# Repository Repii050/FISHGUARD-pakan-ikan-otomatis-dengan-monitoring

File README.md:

# FISHGUARD
<!DOCTYPE html>
<html lang="id">
<head>
    <meta charset="UTF-8">
    <meta name="viewport" content="width=device-width, initial-scale=1.0">
    <meta http-equiv="X-UA-Compatible" content="ie=edge">
    
</head>
<body>
    <div class="container">
        <h1>Rancang bangun pakan ikan otomatis dengan monitoring realtime </h1>
        <p>Ikan Hias dikenal sebagai salah satu spesies ikan yang banyak di budidayakan dan memiliki nilai ekonomis tinggi. Namun, ikan Hias juga memerlukan kondisi lingkungan yang sangat spesifik dan stabil agar dapat tumbuh dengan baik. Fluktuasi suhu air, perubahan kadar pH, serta rendahnya kadar oksigen dalam air dapat berdampak negatif pada kesehatan ikan.</p>
        <h1>Didukung Oleh :</h1>
<p> Dosen Pengampu : Akhmad Hendriawan ST., MT. (NIP.197501272002121003)</p>
<p>Mata kuliah : IoT dan Jaringan Sensor </p><br>
<p>Program Studi : D4 Teknik Elektronika</p><br>
<p>Politeknik Elektronika Negeri Surabaya</p><br>
        <h2>Daftar Nama Anggota Team</h2>  
    <table>
        <thead>
            <tr>
                <th>Nomor</th>
                <th>Nama</th>
                <th>NRP</th>
                <th>Jobdesk</th>
                <th>Nama Akun</th>
                <th>Link Akun</th>
            </tr>
        </thead>
        <tbody>
            <tr>
                <td align = center>1</td>
                <td>Alwansyah Muhammad M.E</td>
                <td>2122600031</td>
                <td>Project Sales</td>
                <td>alwansyahendrawan</td>
                <td>https://github.com/alwansyahendrawan</td>
            </tr>
            <tr>
                <td align = center>2</td>
                <td>I Gede Wahyu Satria Nugraha </td>
                <td>2122600033</td>
                <td>UI/UX Desain</td>
                <td>Gedewsnnn</td>
                <td>https://github.com/Gedewsnnn</td>
            </tr>
            <tr>
                <td align = center>3</td>
                <td>Rafi Satrio</td>
                <td>2122600050</td>
                <td>Hardware Developer</td>
                <td>Repii050</td>
                <td>https://github.com/Repii050</td>
            </tr>
                <tr>
                <td align = center>4</td>
                <td>Dewangga Pratama Ikko Prasetyo</td>
                <td>2122600052</td>
                <td>Data Analyst</td>
                <td>DewanggaPIP</td>
                <td>https://github.com/DewanggaPIP</td>
            </tr>
                <tr>
                <td align = center>5</td>
                <td>Wildan Aldi Nugroho</td>
                <td>2122600055</td>
                <td>Software Developer</td>
                <td>Wildan-Aldi</td>
                <td>https://github.com/Wildan-Aldi</td>
            </tr>
             <tr>
                <td align = center>6</td>
                <td> Dera Berlian </td>
                <td>2122600057</td>
                <td>Project Manager</td>
                <td>DeraBerlian</td>
                <td>https://github.com/DeraBerlian</td>
            </tr>
        </tbody>
    </table>
<h1>Hardware </h1>
<p>Berikut ini adalah hasil skematik rangkaian FishGuard menggunakan software Eagle.</p>
        
<br>
 <p>Berikut ini adalah hasil Board PCB rangkaian FishGuard menggunakan software Eagle.</p><br>                                                                                                                                                               
<br>
<h1>Desain 3D </h1>
1. Desain 3D Tampak Depan <br>

2. Desain 3D Tampak Samping <br>

3. Desain 3D Tampak Belakang <br>

# ANGGOTA KELOMPOK FISH GUARD

# Fleyer

# Link Video Iklan : 
https://youtube.com/shorts/qlZNBy3aBwo?feature=share

# Link Video Pengujian Sistem : 
https://youtu.be/G6Ex1cATNBE

# Link Video Presentasi : 
https://youtu.be/gjWip73ETbg
# Software Aplikasi
https://github.com/Repii050/FISHGUARD-pakan-ikan-otomatis-dengan-monitoring/tree/main/Aplikasi
# DATA 
https://github.com/Repii050/FISHGUARD-pakan-ikan-otomatis-dengan-monitoring/tree/main/Data
# Desain dan Perencanaan 
https://github.com/Repii050/FISHGUARD-pakan-ikan-otomatis-dengan-monitoring/tree/main/Desain%20dan%20Perencanaan
# Hardware
https://github.com/Repii050/FISHGUARD-pakan-ikan-otomatis-dengan-monitoring/tree/main/Hardware#readme
# diagram sistem

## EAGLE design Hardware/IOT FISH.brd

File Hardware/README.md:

# Video Pengujian Komponen

Berikut adalah beberapa video serta progam yang digunakan dalam pengujian berbagai komponen sistem FishGuard.

## FishGuard - Pengujian Servo
https://github.com/user-attachments/assets/23995870-86eb-4068-b8aa-cf2c34f3a0c6

### Program Pengujian servo
Program ini berfungsi untuk melakukan pengujian dengan mengendalikan sebuah servo motor menggunakan Arduino, menggerakkannya dari sudut 0° hingga 180° dan kembali, sambil menampilkan posisi aktuator pada Serial Monitor.
```cpp
#include <Servo.h>

// Membuat objek servo
Servo myServo;

// Mendefinisikan pin servo
const int servoPin = 9;

void setup() {
  // Menentukan pin servo dan menginisialisasi servo
  myServo.attach(servoPin);

  // Memulai komunikasi serial untuk menampilkan posisi di Serial Monitor
  Serial.begin(9600);
}

void loop() {
  // Menggerakkan servo dari 0° ke 180°
  for (int pos = 0; pos <= 180; pos += 1) { // Inkrementasi 1 derajat
    myServo.write(pos);
    Serial.print("Posisi Servo: ");
    Serial.print(pos);
    Serial.println(" derajat");
    delay(15); // Tunggu 15 ms agar servo memiliki waktu untuk bergerak
  }

  // Menggerakkan servo dari 180° ke 0°
  for (int pos = 180; pos >= 0; pos -= 1) { // Dekrementasi 1 derajat
    myServo.write(pos);
    Serial.print("Posisi Servo: ");
    Serial.print(pos);
    Serial.println(" derajat");
    delay(15); // Tunggu 15 ms agar servo memiliki waktu untuk bergerak
  }
}
```

## FishGuard - Pengujian Sensor Ultrasonic HC-SR04
https://github.com/user-attachments/assets/480f4f2f-f9c4-4a9e-84b7-378d93c347e1

### Program Pengujian Sensor Ultrasonic HC-SR04
Program ini berfungsi untuk melakukan pengujian dengan mengukur jarak.
```cpp
// Mendefinisikan pin Trig dan Echo
const int trigPin = 9;
const int echoPin = 10;

// Variabel untuk menyimpan hasil pengukuran jarak
long duration;
float distance;

void setup() {
  // Inisialisasi komunikasi serial
  Serial.begin(9600);

  // Mengatur pin trigPin sebagai output dan echoPin sebagai input
  pinMode(trigPin, OUTPUT);
  pinMode(echoPin, INPUT);
}

void loop() {
  // Membersihkan pin trigPin
  digitalWrite(trigPin, LOW);
  delayMicroseconds(2);

  // Mengirimkan sinyal trigger selama 10 mikrodetik
  digitalWrite(trigPin, HIGH);
  delayMicroseconds(10);
  digitalWrite(trigPin, LOW);

  // Membaca durasi waktu dari sinyal yang diterima oleh echoPin
  duration = pulseIn(echoPin, HIGH);

  // Menghitung jarak (dalam cm) berdasarkan waktu tempuh sinyal
  distance = duration * 0.034 / 2;

  // Menampilkan hasil pengukuran jarak di Serial Monitor
  Serial.print("Jarak: ");
  Serial.print(distance);
  Serial.println(" cm");

  delay(500); // Delay 0,5 detik untuk stabilitas pembacaan
}
```

## FishGuard - Pengujian Sensor DS18B20 Suhu
https://github.com/user-attachments/assets/f8e08aa3-e3c8-4e6e-869c-6c9238689587

### Program Sensor DS18B20 Suhu
Program ini berfungsi untuk melakukan pengujian dengan membaca suhu dari sensor DS18B20 menggunakan Arduino, dan menampilkan hasilnya di Serial Monitor. Sensor ini terhubung melalui protokol OneWire.
```cpp
#include <OneWire.h>
#include <DallasTemperature.h>

// Pin yang terhubung ke pin DATA DS18B20
const int dataPin = 2;

// Membuat instance dari OneWire
OneWire oneWire(dataPin);

// Membuat instance dari DallasTemperature
DallasTemperature sensors(&oneWire);

void setup() {
  // Memulai komunikasi serial
  Serial.begin(9600);

  // Memulai sensor DS18B20
  sensors.begin();
}

void loop() {
  // Meminta sensor untuk melakukan pembacaan suhu
  sensors.requestTemperatures();

  // Membaca suhu dalam Celsius dari sensor pertama (index 0)
  float temperatureC = sensors.getTempCByIndex(0);

  // Menampilkan suhu di Serial Monitor
  Serial.print("Suhu: ");
  Serial.print(temperatureC);
  Serial.println(" °C");

  delay(1000); // Membaca suhu setiap 1 detik
}
```

## FishGuard - Pengujian Sensor TDS Meter
https://github.com/user-attachments/assets/90e463b5-ef5b-4650-b92f-95f3acb5ff2d

### Program Pengujian Sensor TDS Meter
Program ini berfungsi untuk melakukan pengujian dengan membaca nilai Total Dissolved Solids (TDS) dalam larutan menggunakan sensor TDS yang terhubung ke pin analog Arduino. TDS mengukur jumlah partikel terlarut (seperti mineral dan garam) dalam air, biasanya dinyatakan dalam ppm (parts per million).
```cpp
// Mendefinisikan pin analog yang terhubung ke sensor TDS
const int tdsPin = A0; 

// Tegangan input referensi di Arduino (biasanya 5V)
const float vRef = 5.0; 
// Faktor konversi dari tegangan ke TDS, sesuaikan berdasarkan datasheet atau kalibrasi
const float conversionFactor = 0.5; 

void setup() {
  Serial.begin(9600);  // Memulai komunikasi serial untuk membaca hasil TDS
  pinMode(tdsPin, INPUT);  // Menentukan pin TDS sebagai input
}

void loop() {
  // Membaca nilai analog dari pin TDS
  int analogValue = analogRead(tdsPin);
  
  // Mengonversi nilai analog ke tegangan
  float voltage = analogValue * (vRef / 1024.0);
  
  // Menghitung nilai TDS (mg/L atau ppm)
  float tdsValue = voltage * conversionFactor * 1000; // Sesuaikan sesuai kalibrasi
  
  // Menampilkan nilai TDS di Serial Monitor
  Serial.print("TDS Value: ");
  Serial.print(tdsValue);
  Serial.println(" ppm");

  delay(1000);  // Membaca nilai TDS setiap 1 detik
}
```
## FishGuard - Schematic

## FishGuard - PCB Bawah

## FishGuard - PCB Atas

## Progres 1

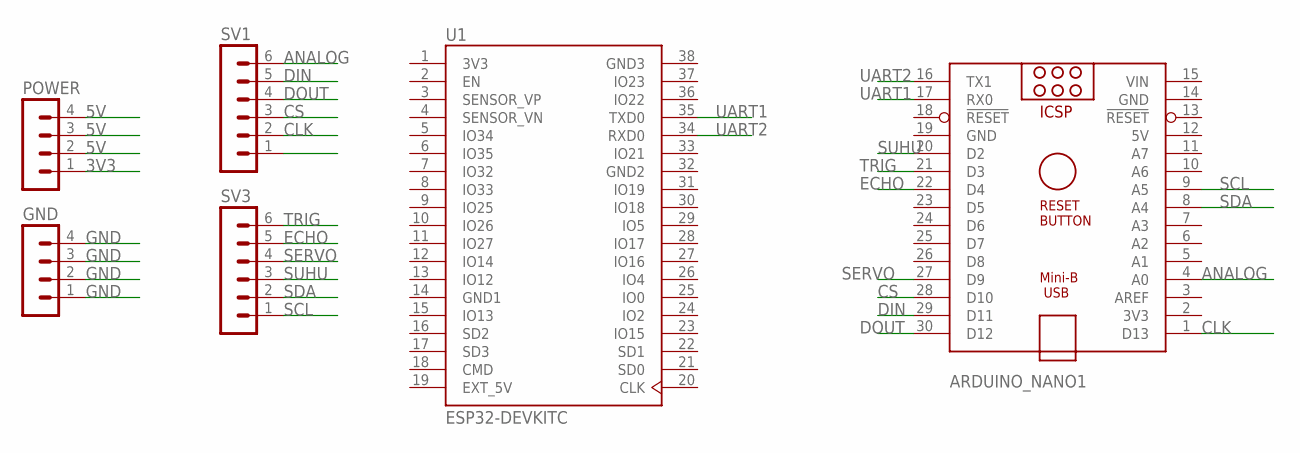
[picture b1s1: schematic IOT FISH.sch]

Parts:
ARDUINO_NANO1: ARDUINO_NANO
GND: MA04-1
POWER: MA04-1
SV1, SV3: MA06-1
U1: ESP32-DEVKITC; MODULE_ESP32-DEVKITC

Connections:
3V3: POWER.1, U1.1 (3V3)
5V: ARDUINO_NANO1.12 (5V), POWER.2, POWER.3, POWER.4
ANALOG: ARDUINO_NANO1.4 (A0), SV1.6
CLK: ARDUINO_NANO1.1 (D13), SV1.2
CS: ARDUINO_NANO1.28 (D10), SV1.3
DIN: ARDUINO_NANO1.29 (D11), SV1.5
DOUT: ARDUINO_NANO1.30 (D12), SV1.4
ECHO: ARDUINO_NANO1.22 (D4), SV3.5
EXT_5V: U1.19 (EXT_5V)
GND: ARDUINO_NANO1.14 (GND), ARDUINO_NANO1.19 (GND), GND.1, GND.2, GND.3, GND.4
GND1: U1.14 (GND1)
GND2: U1.32 (GND2)
GND3: U1.38 (GND3)
SCL: ARDUINO_NANO1.9 (A5), SV3.1
SDA: ARDUINO_NANO1.8 (A4), SV3.2
SERVO: ARDUINO_NANO1.27 (D9), SV3.4
SUHU: ARDUINO_NANO1.20 (D2), SV3.3
TRIG: ARDUINO_NANO1.21 (D3), SV3.6
UART1: ARDUINO_NANO1.17 (RX0), U1.35 (TXD0)
UART2: ARDUINO_NANO1.16 (TX1), U1.34 (RXD0)
VIN: ARDUINO_NANO1.15 (VIN)

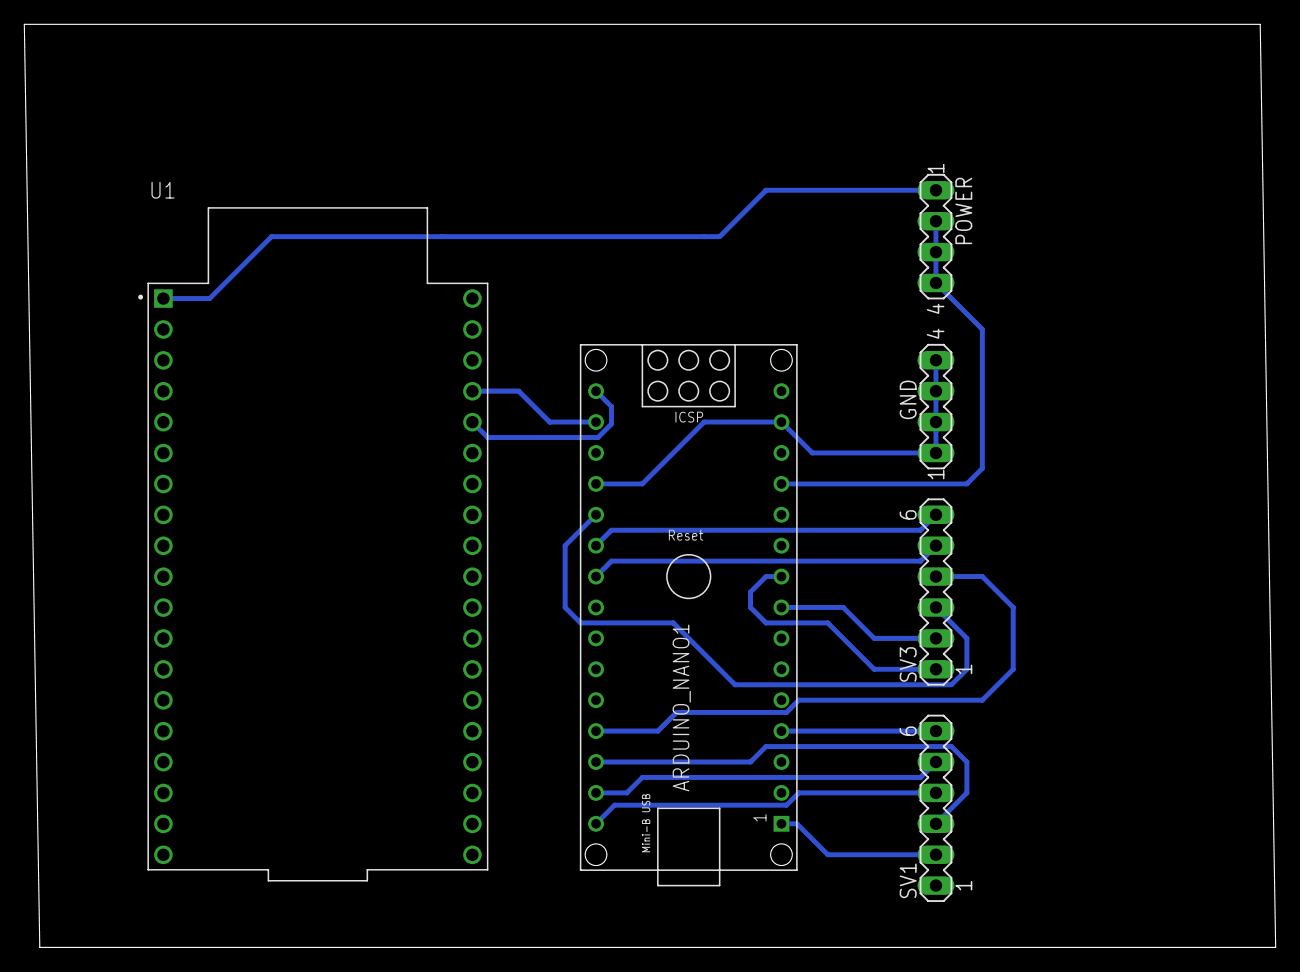
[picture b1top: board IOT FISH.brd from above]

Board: 2 copper layers, 102.8 x 75.9 mm, 6 parts (0 on the bottom side), 16 nets.

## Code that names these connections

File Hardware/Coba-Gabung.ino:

#include <OneWire.h>
#include <DallasTemperature.h>
#include <Wire.h>
#include <LiquidCrystal_I2C.h>
#include <Servo.h>

const int dataPin = 2;// Pin yang terhubung ke pin DATA DS18B20
const int tdsPin = A0; // Mendefinisikan pin analog yang terhubung ke sensor TDS
const float vRef = 5.0; // Tegangan input referensi di Arduino (biasanya 5V)
const float conversionFactor = 0.5; // Faktor konversi dari tegangan ke TDS, sesuaikan berdasarkan datasheet atau kalibrasi
const int trigPin = 9;// Mendefinisikan pin Trig
const int echoPin = 10;// Mendefinisikan pin Echo
long duration;// Variabel untuk menyimpan hasil pengukuran jarak
float distance;// Variabel untuk menyimpan hasil pengukuran jarak
const int servoPin = 5;// Mendefinisikan pin servo

Servo myServo;// Membuat objek servo
OneWire oneWire(dataPin);// Membuat instance dari OneWire
DallasTemperature sensors(&oneWire);// Membuat instance dari DallasTemperature
LiquidCrystal_I2C lcd(0x27, 16, 2);

void setup() {
Serial.begin(9600);// Memulai komunikasi serial
sensors.begin();  // Memulai sensor DS18B20
// Mengatur pin trigPin sebagai output dan echoPin sebagai input
pinMode(trigPin, OUTPUT);
pinMode(echoPin, INPUT);
lcd.init();
lcd.backlight();

}
void loop() {
   pinMode(tdsPin, INPUT);  // Menentukan pin TDS sebagai input
  // Meminta sensor untuk melakukan pembacaan suhu
  sensors.requestTemperatures();
  // Menentukan pin servo dan menginisialisasi servo
  myServo.attach(servoPin);
  // Membaca suhu dalam Celsius dari sensor pertama (index 0)
  float temperatureC = sensors.getTempCByIndex(0);
   // Membaca nilai analog dari pin TDS
  int analogValue = analogRead(tdsPin);
  
  // Mengonversi nilai analog ke tegangan
  float voltage = analogValue * (vRef / 1024.0);
  
  // Menghitung nilai TDS (mg/L atau ppm)
  float tdsValue = voltage * conversionFactor * 1000; // Sesuaikan sesuai kalibrasi

  // Membersihkan pin trigPin
  digitalWrite(trigPin, LOW);
  delayMicroseconds(2);

  // Mengirimkan sinyal trigger selama 10 mikrodetik
  digitalWrite(trigPin, HIGH);
  delayMicroseconds(10);
  digitalWrite(trigPin, LOW);

  // Membaca durasi waktu dari sinyal yang diterima oleh echoPin
  duration = pulseIn(echoPin, HIGH);

  // Menghitung jarak (dalam cm) berdasarkan waktu tempuh sinyal
  distance = duration * 0.034 / 2;

  // Menampilkan hasil pengukuran jarak di Serial Monitor
  Serial.print("Jarak: ");
  Serial.print(distance);
  Serial.println(" cm");

  delay(500);
  
  // Menampilkan nilai TDS di Serial Monitor
  Serial.print("TDS Value: ");
  Serial.print(tdsValue);
  Serial.println(" ppm");

  delay(1000);

  // Menampilkan suhu di lcd
  lcd.setCursor(0, 0);
  lcd.print("Suhu: ");
  lcd.print(temperatureC);
  lcd.print(" C");

  // Menampilkan suhu di Serial Monitor
  Serial.print("Suhu: ");
  Serial.print(temperatureC);
  Serial.println(" °C");

// Menampilkan suhu di lcd
  lcd.setCursor(0, 1);
  lcd.print("TDS Value: ");
  lcd.print(tdsValue);
  lcd.print(" ppm");

  delay(1000); // Membaca suhu setiap 1 detik
// Menampilkan nilai TDS di Serial Monitor
  Serial.print("TDS Value: ");
  Serial.print(tdsValue);
  Serial.println(" ppm");

  delay(1000);
  //  // Menggerakkan servo dari 0° ke 180°
  // for (int pos = 0; pos <= 180; pos += 1) { // Inkrementasi 1 derajat
  //   myServo.write(pos);
  //   Serial.print("Posisi Servo: ");
  //   Serial.print(pos);
  //   Serial.println(" derajat");
  //   delay(15); // Tunggu 15 ms agar servo memiliki waktu untuk bergerak
  // }

  // // Menggerakkan servo dari 180° ke 0°
  // for (int pos = 180; pos >= 0; pos -= 1) { // Dekrementasi 1 derajat
  //   myServo.write(pos);
  //   Serial.print("Posisi Servo: ");
  //   Serial.print(pos);
  //   Serial.println(" derajat");
  //   delay(15); // Tunggu 15 ms agar servo memiliki waktu untuk bergerak
  // }

}

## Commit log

2024-10-10 README.md
2024-10-12 Skematik
2024-10-12 BOARD
2024-10-13 Create Hardware
2024-10-13 Create 3d
2024-10-13 Create Schematic
2024-10-13 Create MQTT
2024-10-13 Create Lib
2024-10-14 desain fIGMA
    https://www.figma.com/proto/BWjkiZiIXptGYSlhn2zAM4/Untitled?node-id=5-275&node-type=canvas&t=38AJkFG8a8XKul6S-1&scaling=scale-down&content-scaling=fixed&page-id=0%3A1&starting-point-node-id=4%3A310
2024-10-17 LCD I2C - Library
    LCD I2C - Library
2024-10-18 RTC-lib 1
    RTC-lib 1
2024-10-18 RTC-lib 2
    RTC-lib 2
2024-10-22 DS18B20-lib
    DS18B20-lib
2024-10-29 pH Sensor-lib 1
    pH Sensor-lib 1
2024-10-29 pH Sensor-lib 2
    pH Sensor-lib 2
2024-10-29 pH Sensor-lib 3
    pH Sensor-lib 3
2024-10-31 Program Uji Coba Sensor
2024-11-02 Create UI/UX
2024-11-08 Rename Readme to Readme.md
2024-11-08 ANGGOTA KELOMPOK FISH GUARD.md
2024-11-10 Rename Tampak Atas.png to Design 3D Tampak Atas.png
2024-11-10 Rename Tampak Belakang.png to Design 3D Tampak Belakang.png
2024-11-10 Rename Tampak Samping.png to Design 3D Tampak Samping.png
2024-11-10 Rename WhatsApp Image 2024-11-03 at 12.50.31 AM.jpeg to Design Schematic Eagle
2024-11-10 Rename WhatsApp Image 2024-11-03 at 12.49.42 AM.jpeg to Design Board PCB
2024-11-10 Rename Timeline.png to Timeline November Minggu ke-2.png
